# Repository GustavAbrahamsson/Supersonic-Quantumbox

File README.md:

# Supersonic-Quantumbox

Multi-use digital guitar pedal

## Features
This pedal is an experiment in digital sound processing, powered by an ESP32-S2 running arduino. Designed to be ultra-flexible, it has a wide array of controls and indicators including knobs, lights, a screen, true bypass switch and easily available expansions. The high performance analog components from texas instruments handle 24bit data at 48KHz. 

## Todo
This project is still WIP, alot of things can be improved to make the pedal as easy and fun as possible.

- [x] Menu system for managing multiple effects at the same time
- [x] Nice looking and sturdy enclosure
- [ ] Add lots different of effects
- [ ] Expansion port for expression pedals, switches and more
- [ ] PCB revision with ESP32-S3, better power supply filtering, footprint fixes
- [ ] Wi-Fi configuration?

Apart from this the pedal is designed to be an exploration platform for different DSP techniques and algorithms, so new effects will hopefully be added continously.

## Creators
- Adam Anderson (@adaand00): PCB, low-level drivers
- Gustav Abrahamsson (@GustavAbrahamsson): PCB, Enclosure design

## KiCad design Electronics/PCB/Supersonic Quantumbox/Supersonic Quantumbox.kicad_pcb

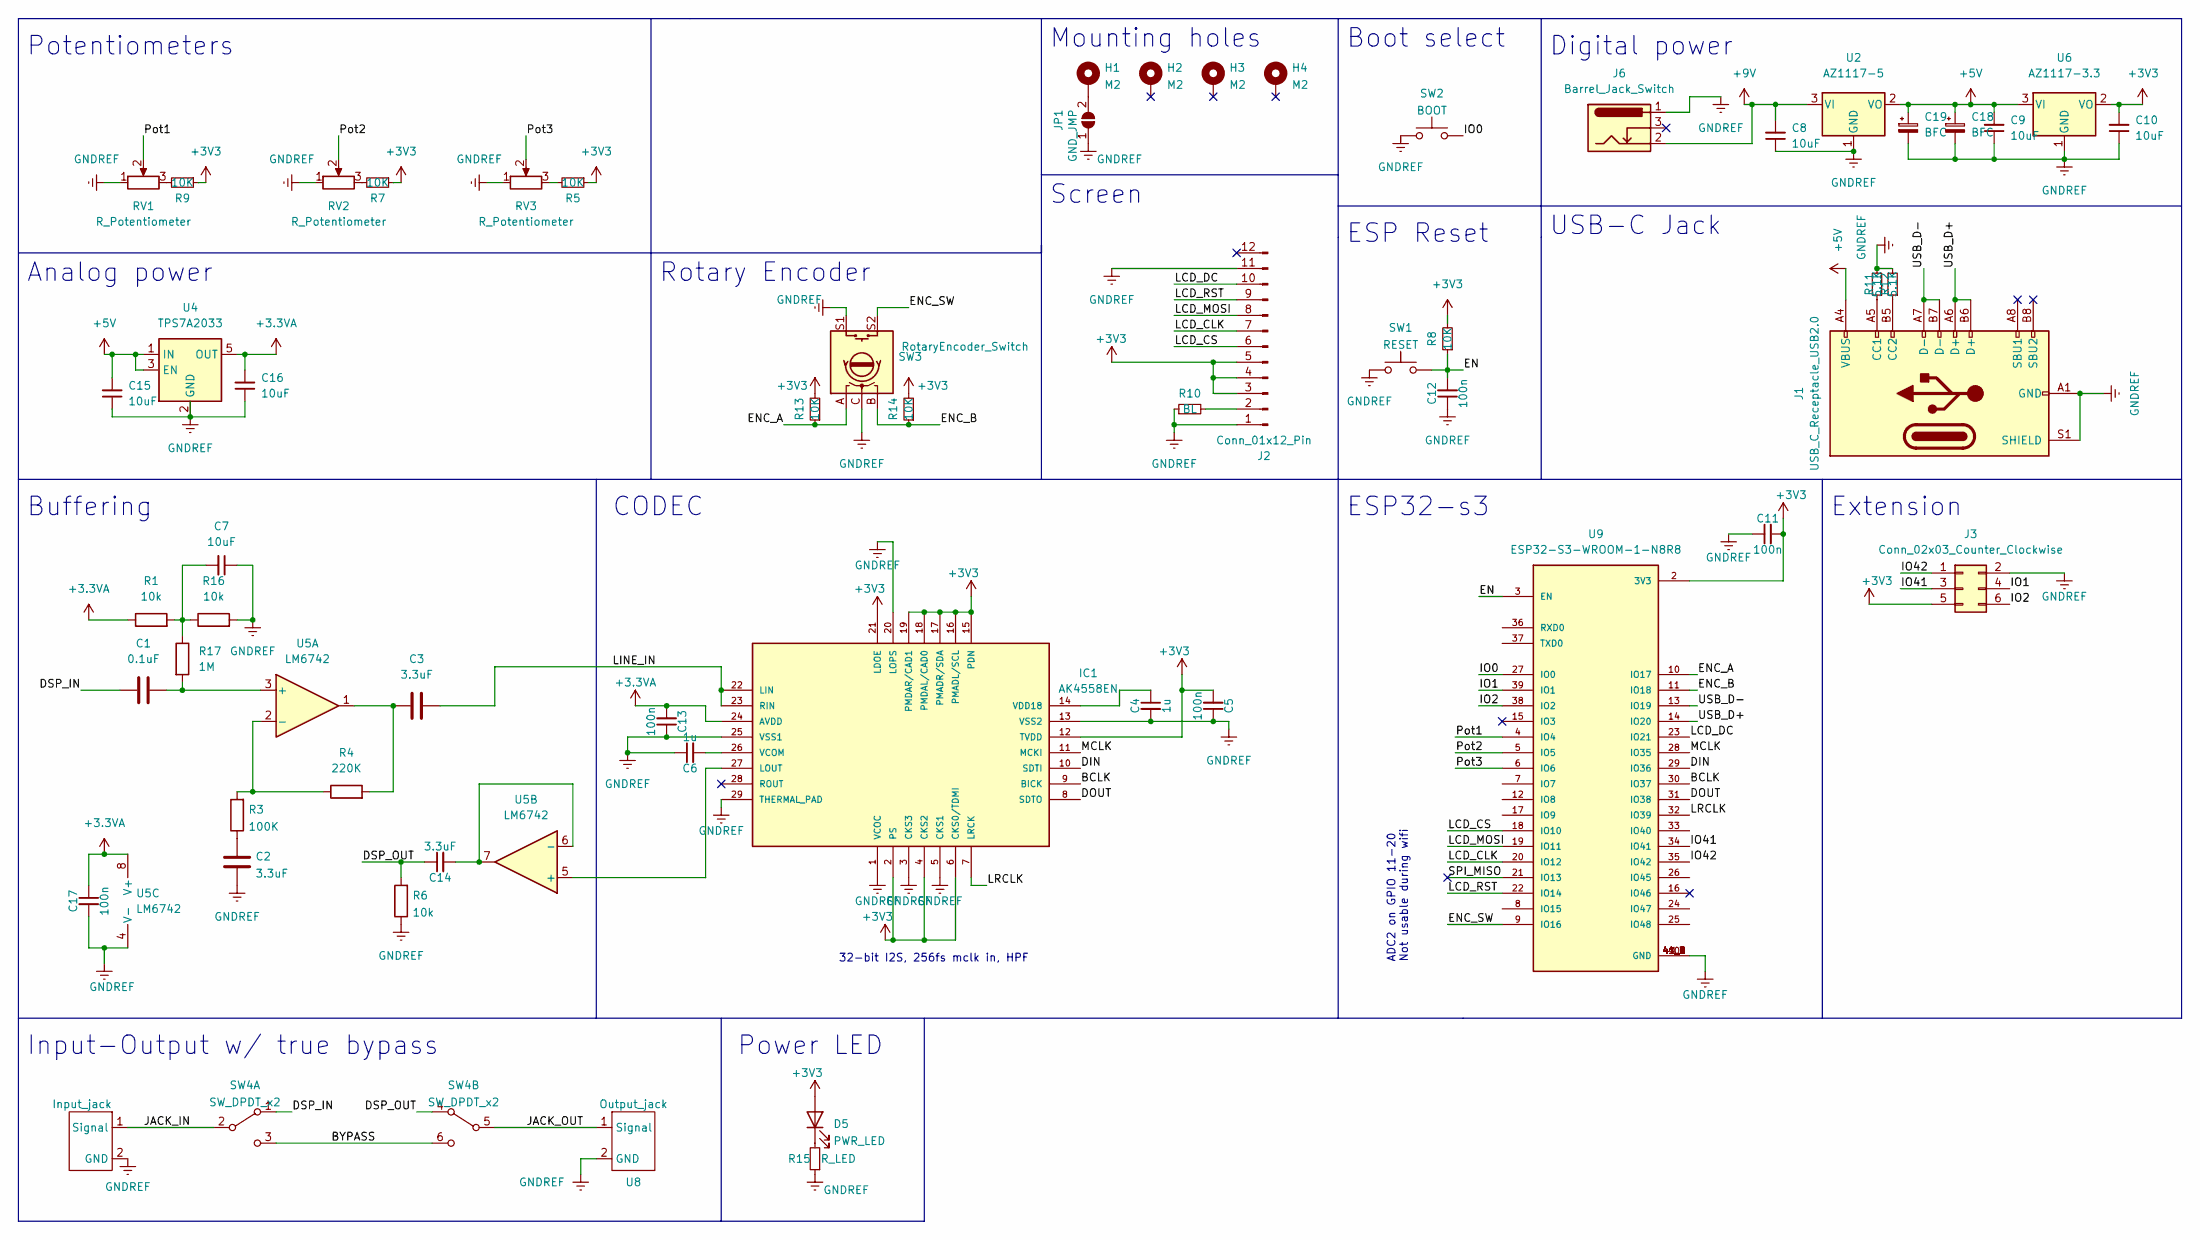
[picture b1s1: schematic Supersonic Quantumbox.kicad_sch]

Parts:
C1: 0.1uF; C_Rect_L10.3mm_W5.7mm_P7.50mm_MKS4
C2, C3, C14: 3.3uF; C_Rect_L26.5mm_W10.5mm_P22.50mm_MKS4
C4, C6: 1u; C_0603_1608Metric
C5, C11, C12, C13, C17: 100n; C_0603_1608Metric
C7, C8, C9, C10, C15, C16: 10uF; C_1206_3216Metric
C18, C19: BFC; CP_Radial_D6.3mm_P2.50mm
D5: PWR_LED; LED_0805_2012Metric_Pad1.15x1.40mm_HandSolder
H1, H2, H3, H4: M2; MountingHole_2.2mm_M2_Pad_Via
IC1: AK4558EN; QFN50P500X500X75-29N; MANUFACTURER_PART_NUMBER AK4558EN
J1: USB_C_Receptacle_USB2.0; USB_C_Receptacle_HRO_TYPE-C-31-M-12
J2: Conn_01x12_Pin; TE_1-1734839-2_1x12-1MP_P0.5mm_Horizontal
J3: Conn_02x03_Counter_Clockwise; PinSocket_2x03_P2.54mm_Horizontal
J6: Barrel_Jack_Switch; BarrelJack_Horizontal
JP1: GND_JMP; SolderJumper-2_P1.3mm_Open_TrianglePad1.0x1.5mm
R1, R6, R16: 10k; R_0603_1608Metric
R3: 100K; R_0603_1608Metric
R4: 220K; R_0603_1608Metric
R5, R7, R8, R9, R13, R14: 10K; R_0603_1608Metric
R10: BL; R_0603_1608Metric
R11, R12: 5.1K; R_0603_1608Metric
R15: R_LED; R_0603_1608Metric
R17: 1M; R_0603_1608Metric
RV1, RV2, RV3: R_Potentiometer; Potentiometer_Alps_RK09K_Single_Vertical
SW1: RESET; SW_SPST_EVQP7C
SW2: BOOT; SW_SPST_EVQP7C
SW3: RotaryEncoder_Switch; RotaryEncoder_Alps_EC12E-Switch_Vertical_H20mm
SW4: SW_DPDT_x2; SW_Push_2P2T_Toggle_MHPS2285
U1: Input_jack; MonoJack-SYS212
U2: AZ1117-5; SOT-223-3_TabPin2
U4: TPS7A2033; SOT-23-5
U5: LM6742; SOIC-8_3.9x4.9mm_P1.27mm
U6: AZ1117-3.3; SOT-223-3_TabPin2
U8: Output_jack; MonoJack-SYS212
U9: ESP32-S3-WROOM-1-N8R8; XCVR_ESP32S3WROOM1N8R8

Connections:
+3.3VA: C13.2, C16.2, C17.1, IC1.24 (AVDD), R1.1, U4.5 (OUT), U5.8 (V+)
+3V3: C5.2, C10.2, C11.2, D5.2 (A), IC1.2 (PS), IC1.4 (CKS2), IC1.6 (CKS0/TDMI), IC1.12 (TVDD), IC1.15 (PDN), IC1.16 (PMADL/SCL), IC1.17 (PMADR/SDA), IC1.18 (PMDAL/CAD0), IC1.19 (PMDAR/CAD1), IC1.21 (LDOE), J2.3, J2.4, J2.5, J3.5, R5.1, R7.1, R8.2, R9.1, R13.2, R14.2, U6.2 (VO), U9.2 (3V3)
+5V: C9.2, C15.2, C18.1, C19.1, J1.A4 (VBUS), J1.A9 (VBUS), J1.B4 (VBUS), J1.B9 (VBUS), U2.2 (VO), U4.1 (IN), U4.3 (EN), U6.3 (VI)
+9V: C8.2, J6.2, U2.3 (VI)
/BCLK: IC1.9 (BICK), U9.30 (IO37)
/BYPASS: SW4.3 (C), SW4.6 (C)
/DIN: IC1.10 (SDTI), U9.29 (IO36)
/DOUT: IC1.8 (SDTO), U9.31 (IO38)
/DSP_IN: C1.1, SW4.1 (A)
/DSP_OUT: C14.1, R6.2, SW4.4 (A)
/EN: C12.2, R8.1, SW1.2, U9.3 (EN)
/ENC_A: R13.1, SW3.A, U9.10 (IO17)
/ENC_B: R14.1, SW3.B, U9.11 (IO18)
/ENC_SW: SW3.S2, U9.9 (IO16)
/IO0: SW2.2, U9.27 (IO0)
/IO1: J3.4, U9.39 (IO1)
/IO2: J3.6, U9.38 (IO2)
/IO41: J3.3, U9.34 (IO41)
/IO42: J3.1, U9.35 (IO42)
/JACK_IN: SW4.2 (B), U1.1 (Signal)
/JACK_OUT: SW4.5 (B), U8.1 (Signal)
/LCD_CLK: J2.7, U9.20 (IO12)
/LCD_CS: J2.6, U9.18 (IO10)
/LCD_DC: J2.10, U9.23 (IO21)
/LCD_MOSI: J2.8, U9.19 (IO11)
/LCD_RST: J2.9, U9.22 (IO14)
/LINE_IN: C3.2, IC1.22 (LIN), IC1.23 (RIN)
/LRCLK: IC1.7 (LRCK), U9.32 (IO39)
/MCLK: IC1.11 (MCKI), U9.28 (IO35)
/Pot1: RV1.2, U9.4 (IO4)
/Pot2: RV2.2, U9.5 (IO5)
/Pot3: RV3.2, U9.6 (IO6)
/SPI_MISO: U9.21 (IO13)
/USB_D+: J1.A6 (D+), J1.B6 (D+), U9.14 (IO20)
/USB_D-: J1.A7 (D-), J1.B7 (D-), U9.13 (IO19)
GNDREF: C2.1, C4.2, C5.1, C6.1, C7.1, C8.1, C9.1, C10.1, C11.1, C12.1, C13.1, C15.1, C16.1, C17.2, C18.2, C19.2, IC1.1 (VCOC), IC1.3 (CKS3), IC1.5 (CKS1), IC1.13 (VSS2), IC1.20 (LOPS), IC1.25 (VSS1), IC1.29 (THERMAL_PAD), J1.A1 (GND), J1.A12 (GND), J1.B1 (GND), J1.B12 (GND), J1.S1 (SHIELD), J2.1, J2.11, J3.2, J6.1, JP1.1 (A), R6.1, R10.1, R11.2, R12.2, R15.1, R16.2, RV1.1, RV2.1, RV3.1, SW1.1, SW2.1, SW3.C, SW3.S1, U1.2 (GND), U2.1 (GND), U4.2 (GND), U5.4 (V-), U6.1 (GND), U8.2 (GND), U9.1 (GND), U9.40 (GND), U9.41_1 (GND), U9.41_2 (GND), U9.41_3 (GND), U9.41_4 (GND), U9.41_5 (GND), U9.41_6 (GND), U9.41_7 (GND), U9.41_8 (GND), U9.41_9 (GND)
unnamed: C2.2, R3.1
unnamed: C3.1, R4.2, U5.1
unnamed: C7.2, R1.2, R16.1, R17.1
unnamed: D5.1 (K), R15.2
unnamed: IC1.27 (LOUT), U5.5 (+)
unnamed: C6.2, IC1.26 (VCOM)
unnamed: C4.1, IC1.14 (VDD18)
unnamed: J1.A5 (CC1), R11.1
unnamed: J1.B5 (CC2), R12.1
unnamed: J2.2, R10.2
unnamed: H1.1, JP1.2 (B)
unnamed: R5.2, RV3.3
unnamed: R7.2, RV2.3
unnamed: R9.2, RV1.3
unnamed: C1.2, R17.2, U5.3 (+)
unnamed: R3.2, R4.1, U5.2 (-)
unnamed: C14.2, U5.6 (-), U5.7

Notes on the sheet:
Analog power
CODEC
Mounting holes
32-bit I2S, 256fs mclk in, HPF
ESP Reset
Input-Output w/ true bypass
Screen
ESP32-s3
Extension
ADC2 on GPIO 11-20 Not usable during wifi
Power LED
Rotary Encoder
Boot select
Potentiometers
Digital power
Buffering
USB-C Jack

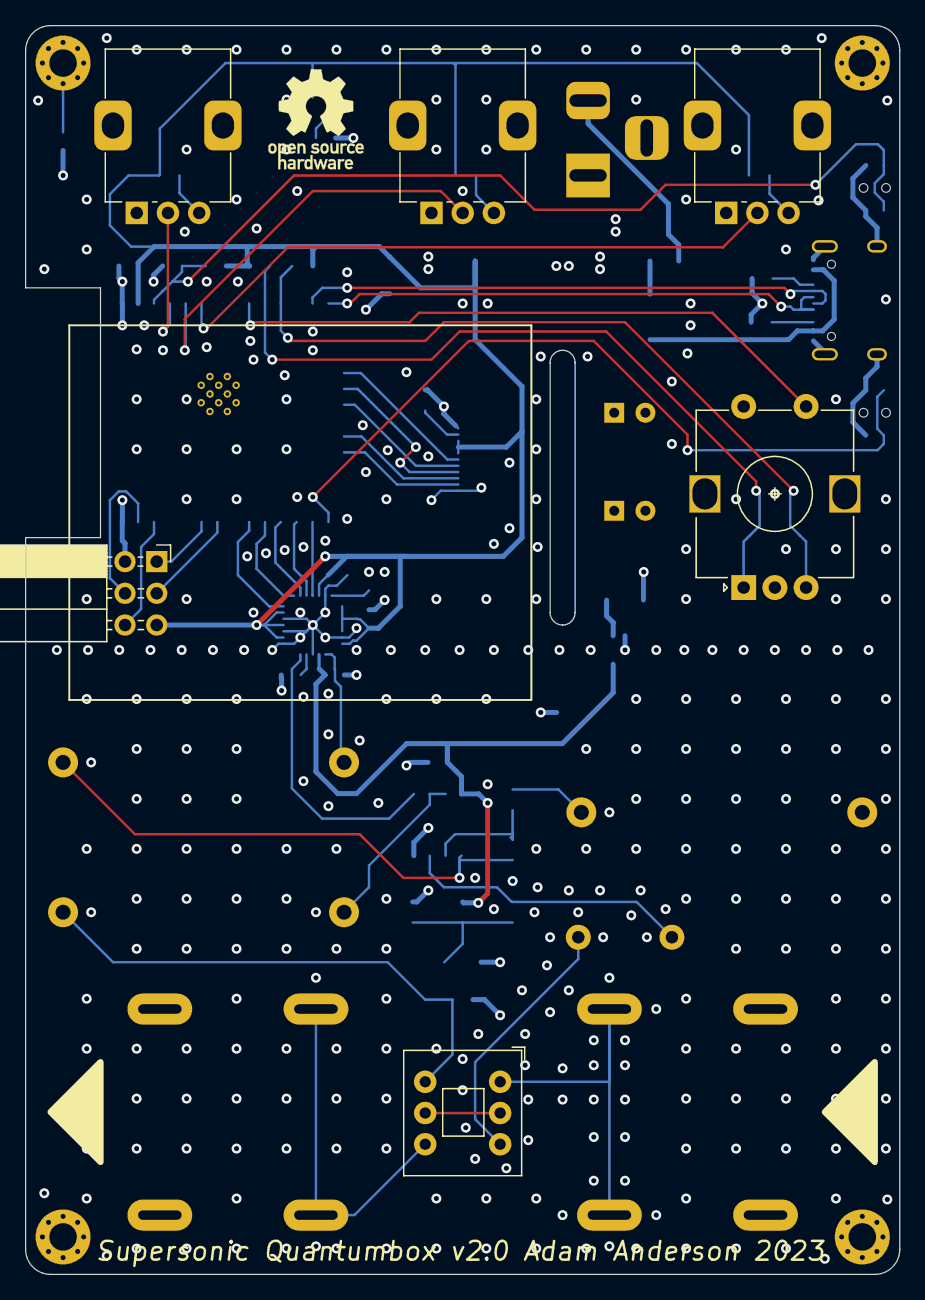
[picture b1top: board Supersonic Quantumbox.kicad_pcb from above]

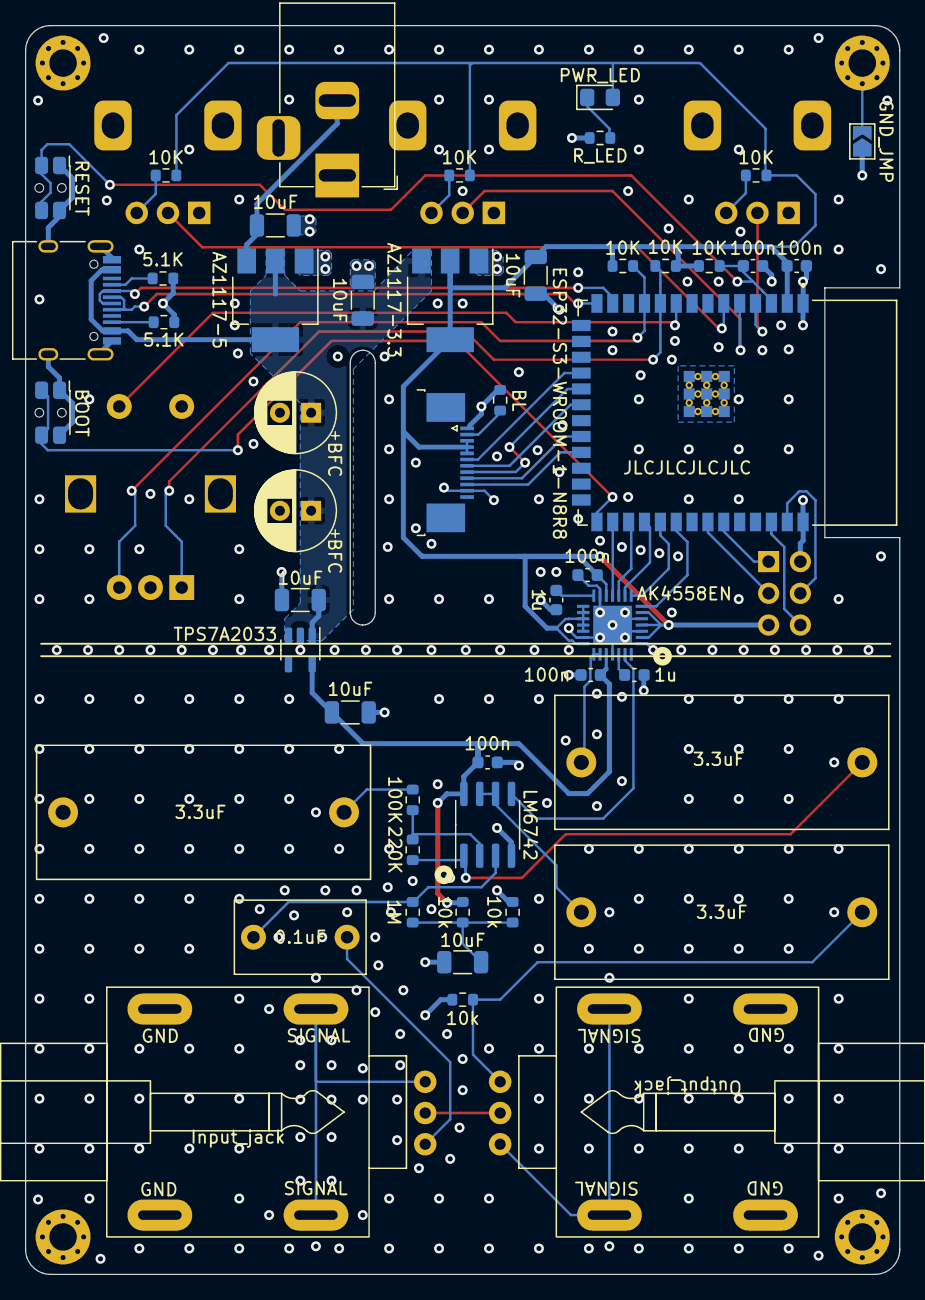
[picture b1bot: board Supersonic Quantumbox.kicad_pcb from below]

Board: 4 copper layers, 70.0 x 100.0 mm, 60 parts (50 on the bottom side), 52 nets.

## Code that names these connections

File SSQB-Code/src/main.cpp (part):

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bool POTS_ENABLED[6] = {true, true, true, false, false, false};

// ----------------Pins-----------------------
#define POT1      GPIO_NUM_1
#define POT2      GPIO_NUM_2
#define POT3      GPIO_NUM_3
#define POT4      GPIO_NUM_4
#define PIXELPIN  GPIO_NUM_5
#define SCL       GPIO_NUM_6
#define SDA       GPIO_NUM_7
#define POT6      GPIO_NUM_8
#define POT5      GPIO_NUM_9
#define ENC_B     GPIO_NUM_10
#define ENC_A     GPIO_NUM_11
#define ENC_SW    GPIO_NUM_12
#define LED1      GPIO_NUM_13
#define LED2      GPIO_NUM_14
#define BCLK      GPIO_NUM_15
#define DIN       GPIO_NUM_16
#define DOUT      GPIO_NUM_17
#define LRCLK     GPIO_NUM_18
#define TRUE_BP   GPIO_NUM_37 // Used on Gustav's pedal

// ----------Global variables-----------------
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int32_t i2s_read_buff[BUFFSIZE*2];
float avgDspTime = 0;

// True: true bypass, the signal is skipping the pedal
// False: the signal is passing through the pedal
volatile bool trueBypass = false;

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// potentiometers
float pots[6];
#define F_POTS (1.0f/8196.0f)
gpio_num_t potPins[6] = {POT1, POT2, POT3, POT4, POT5, POT6};

//deadband for pots
bool potsChanged[6] = {false, false, false, false, false, false};
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  #ifdef USE_ENCODER
    encoder.attachHalfQuad(ENC_A, ENC_B);
    encoder.clearCount();
    pinMode(ENC_SW, INPUT_PULLUP);
    debugPrint("Encoder initialized");
  #endif

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
  delay(1000);

  // If the state of the switch (true bypass) is measured at pin 'TRUE_BP'
  #ifdef USE_TRUE_BP
    pinMode(TRUE_BP, INPUT);
    trueBypass = digitalRead(TRUE_BP);
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
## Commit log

2022-11-01 Init project and PCB
2022-11-01 Develop PCB
2022-11-01 Start work on PCB
2022-11-02 POT and screen adjustment
2022-11-02 Change PCB layout
2022-11-02 Routing
2022-11-03 Begin PWR tracing
2022-11-03 Final routing
2022-11-03 Almost finish PCB
2022-11-04 Final touches
2022-11-04 Add Gerbs
2022-11-06 Add ibom
2022-11-23 Start code, add pins
2022-11-24 Encoder, not working
2022-11-24 Encoder and i2s compiling
2022-11-27 I2S write working
2022-11-29 Restructure, measure time
2022-12-05 Input and output works
2022-12-07 Some more peripherals
2022-12-09 Add pictures
2022-12-09 Edit picture
2022-12-10 Begin case design
2022-12-12 Use LEDS
2022-12-12 Add LED resistor value and Improvements.txt
2022-12-13 Rework DSP function structure
2022-12-13 slight modification to global variables in DSP()
2022-12-15 Clip and some more globals
2022-12-15 Add case 1.0 files
2022-12-16 Start prototype effect class
2022-12-17 Peripheral tweaks, more work on effect classes
2023-03-09 Some work
2023-03-14 Init Saturation effect with plotter
2023-09-24 convert signals to floats, add saturation DSP
2023-09-24 Clean variables
2023-09-24 Minor changes to basic effect modules
2023-09-24 Bug fix
2023-09-24 DelayEffect working ok
2023-09-26 Start work on menu system
2023-09-27 Work on menu system
2023-09-27 Add red LED to show true bypass state
2023-09-27 Compiling
2023-09-28 New Menu compiling and running
2023-09-28 Add FreeRTOS scheduling and fix slow button
2023-09-29 Deadband pots, small fixes
2023-09-30 Basically working the way it should
2023-09-30 Update progress
2023-09-30 Passthrough, minor improvements for effects
2023-09-30 Square effect (be careful)
2023-09-30 Interrupt handler for switch, tweak RTOS
2023-09-30 Broken RTOS testing
2023-10-01 Implement NoiseGate
2023-10-03 Initial peaking filter, parameters not perfect
2023-10-03 Peaking sounds good
2023-10-16 Add utility classes and functions for effects
2023-10-16 Add diffuser effect
2023-10-16 Add simple scope
2023-11-11 Start work on parameter class
2023-11-27 V2 schematic complete
2023-11-28 Routing complete
2023-12-03 PCB finished
